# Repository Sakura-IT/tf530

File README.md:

# TF530 Revision 3

WARNING: This board has not been CE tested. It may cause damage to your A500. I take no responsibility for this. 

This repository contains all the files needed to produce a copy of my accelerator board.

The CPLD Required is a XC9572XL-10VQ64.  The CPLD XC9572XL-10VQG64 is the readily available RoHS "Green" lead-free equivalent.

Everything in this repository is released under the GNU GPLv2. You may create or base commercial PCBs from the work in this repository but you must make the sources for all derivative work available. I have noticed some forks have removed copyright notices. This is a breach of the GPL.

## Firmware / Requirements

  * Xilinx ISE, 14.7 (the final version - other versions may work but this is the one I support)
  * JTAG Adaptor

[For more information visit my channel](https://www.youtube.com/c/TerribleFire)

## License

This project and all the files contained are released under the GNU GPLv2. If you build a modified version of the board you must supply the end user with all the sources (this can be a web link).

## The TerribleFire 530 board (Revision 3)

Completely untested board link.... use with caution!!!! Do not come crying to me if it didnt work!!

http://dirtypcbs.com/store/designer/details/12476/2654/tf530-rev3-zip

## The TerribleFire 530 board (Revision 2)

This board is now in Beta. It may not work in all circumstances but it has been verified to boot AmigaOS 1.3, 2.05 and 3.1 and run various games and desktop apps at 25Mhz. Operation is not guarunteed to be crash free but will work in most "happy path" situations.

I have only verified the HD interface with Compact Flash cards.
I have verified this board boots on Amiga 500 Rev 5, 6a, 8.1a

I accept no responsibiltiy for any damage to any equipment that results from the use of this board. IT IS ENTIRELY AT YOUR OWN RISK!

## Installation

As of Revision 3 installation no longer needs the OVR and INT2 signals connected to the Amiga motherboard. The headers remain on the TF530 for testing but do not need to be connected although it should make little difference if they are connected. Well behaved Autoconfig devices will work alongside the TF530. The autoconfig space asserts the internal OVR signal when there are PICs remaining to be configured. After which the autoconfig will probe the standard bus. This revision should work on the A2000 (untested).

IPL0 has not been routed because we only ever need to assert INT2 and/or INT6.

## What does the board look like

The TF530 Rev 3 looks like...

## The Rev 3 BOM (WARNING! This is untested)

| Qty | Value           | Device             | Package              | Parts                                                            | Description                   |
|-----|-----------------|--------------------|----------------------|------------------------------------------------------------------|-------------------------------|
| 1   |                 | MC68030RC          | MPGA128              | IC1                                                              | 68030 PROCESSOR               |
| 1   |                 | MC68882FN          | PLCC68-S             | IC2                                                              | 68882 CO-PROCESSOR (FPU) + PLCC68 Thru Hole Socket |
| 2   | 0.1uF           | 0.1UF-25V(+80/-20%)| 0603-CAP             | C16, C17                                                         | CAP-00810                     |
| 15  | 10uF            | CAP_CERAMIC1206    | 1206                 | C1, C2, C3, C4, C5, C6, C7, C8, C9, C10, C11, C12, C13, C14, C15 | Ceramic Capacitors            |
| 3   | 1K              | RESISTOR1206       | 1206                 | R1, R2, R3                                                                  | Resistors                     |
| 2   | 74LVC1G17DBV    | 74LVC1G17DBV       | SOT23-5              | IC4, IC5                                                         | Single Schmitt-Trigger Buffer |
| 4   | AS7C4096A-12TCN | AS7C4096A-12TCN    | TSOP44-II            | IC6, IC7, IC8, IC9                                               | SRAM 512k x 8, 5V DO NOT USE ISSI Chips!!      |
| 1   | BYPASS          | JUMPER-2PTH        | 1X02                 | BYPASS                                                           | Jumper                        |
| 3   | CAY16-102J4LF   | CAY16-102J4LF      | RESCAXE80P320X160-8N | RN1, RN2, RN3                                                    | Res Thick Film Array 1K Ohm  |
| 1   | CDIS            | JUMPER-2PTH        | 1X02                 | JP5                                                              | Jumper                        |
| 1   | CLOCKSEL        | JUMPER-3PTH        | 1X03                 | JP1                                                              | Jumper                        |
| 1   | EXT5V           | JUMPER-2PTH        | 1X02                 | PWR1                                                             | Jumper                        |
| 1   | IDE CONNECTOR   | PINHD-2X20         | 2X20                 | IDECONNECTOR                                                     | PIN HEADER                    |
| 1   | INF             | 0.05OHM-1/5W-1%    | 0603                 | RCLKLOAD                                                         | Not Required - Experimental   |
| 1   | JTAG            | HEADER-1X6ROUND    | 1X06_ROUND           | JTAG                                                             | PIN HEADER                    |
| 1   | LM1117-3.3      | V_REG_LM1117SOT223 | SOT223               | IC3                                                              | 3.3V Voltage Regulator LM1117 |
| 1   | MC68000         | MC68000P           | DIL64                | X1                                                               | 68xxx CPU Slot Strip Headers  |
| 1   | MMUDIS          | JUMPER-2PTH        | 1X02                 | JP3                                                              | Jumper                        |
| 1   | SPI PORT        | PINHD-2X6          | 2X06                 | SPIPORT                                                          | PIN HEADER                    |
| 1   | TP1             | JUMPER-2PTH        | 1X02                 | TP1                                                              | Jumper                        |
| 1   | X25MHZ          | OSCILLATOR         | OSC_7X5MM            | OSC1                                                             | Oscillator e.g. 25MHz         |
| 2   | XC9572XL-VQ64   | XC9572XL-VQ64      | VQ64                 | XC9572XL(BUS), XC9572XL(RAM)                                     | Xilinx CPLD                   |

### Notes

* _The CPU and (optional) FPU must be 25MHz/33Mhz capable._

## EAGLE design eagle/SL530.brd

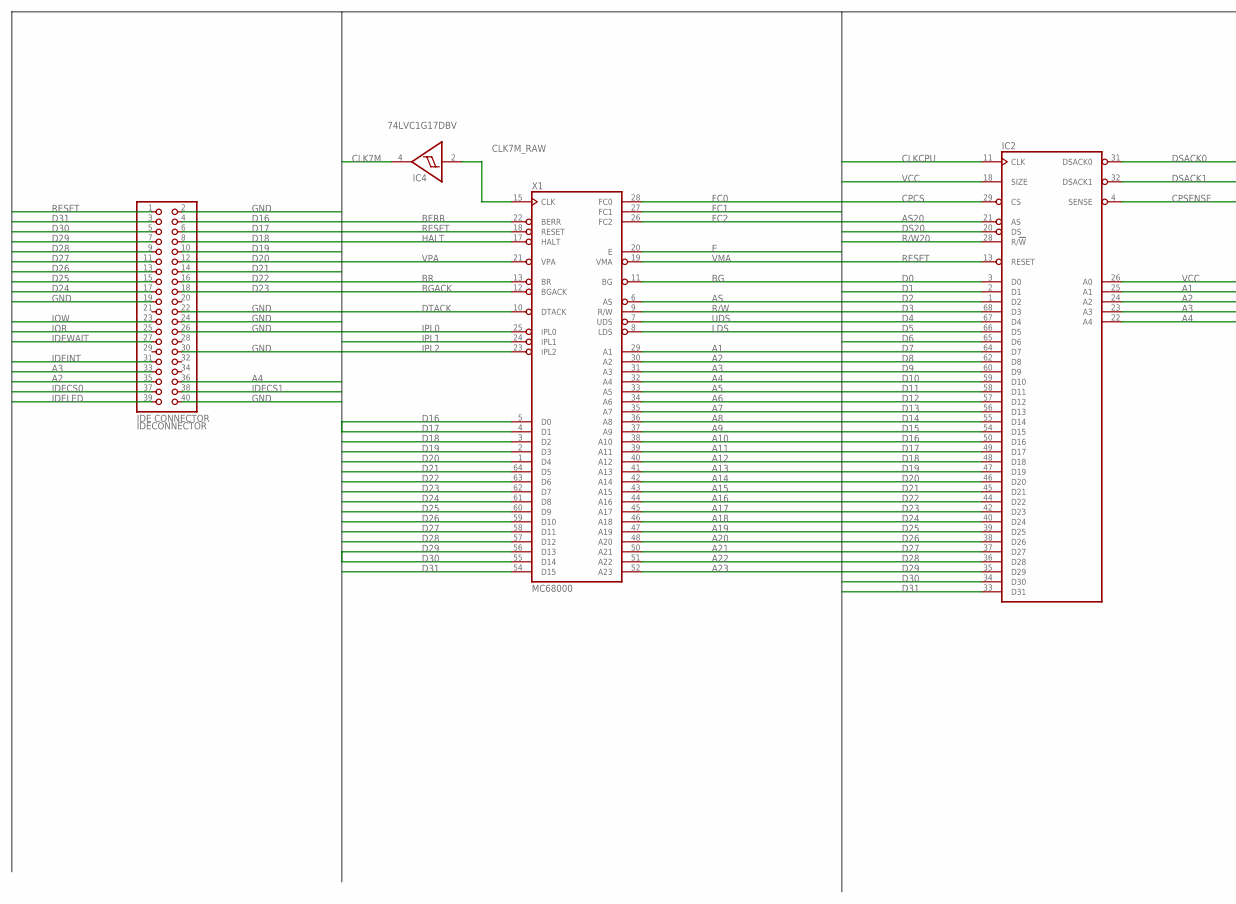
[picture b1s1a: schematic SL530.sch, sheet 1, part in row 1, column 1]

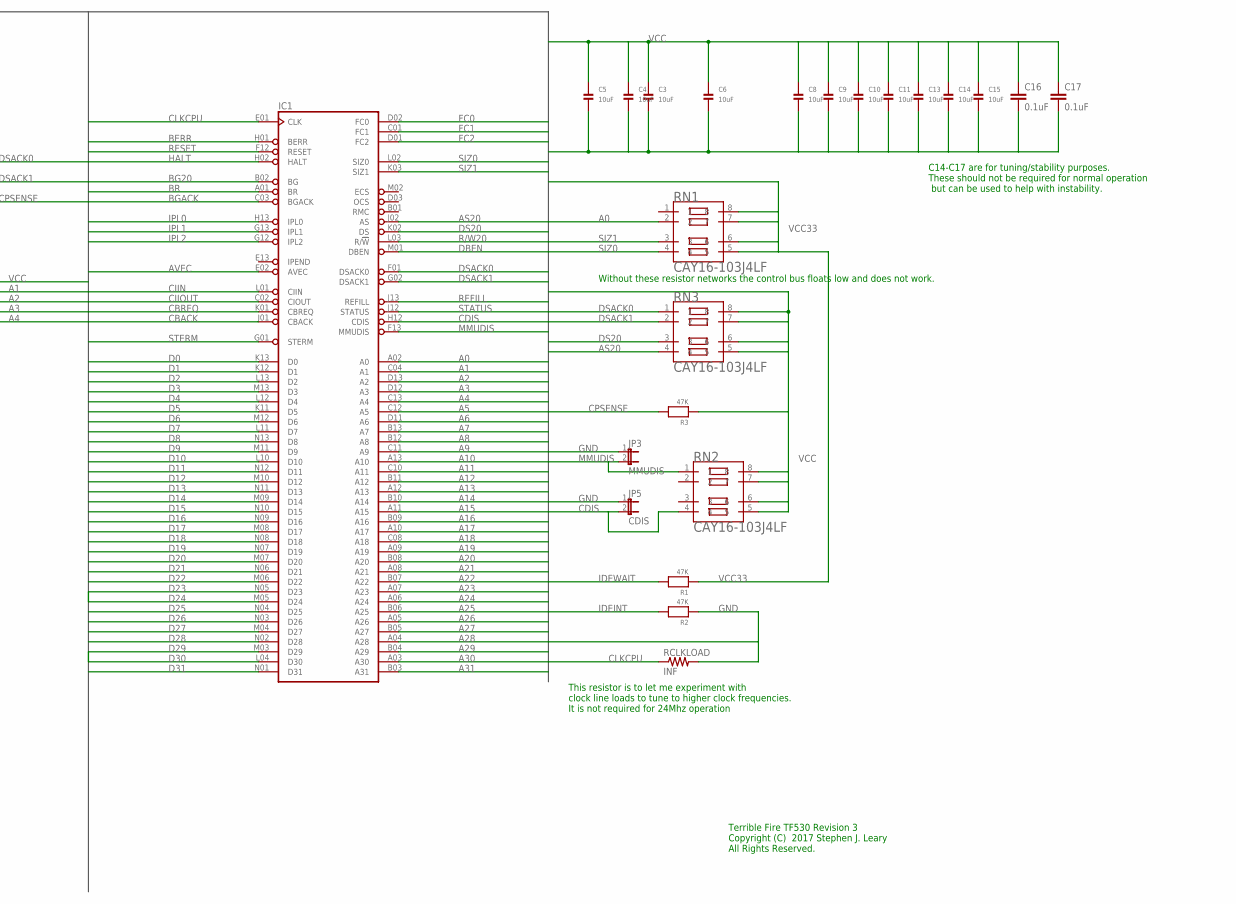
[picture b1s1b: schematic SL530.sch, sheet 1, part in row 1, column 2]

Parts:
C3, C4, C5, C6, C8, C9, C10, C11, C13, C14, C15: 10uF; 1206
C16, C17: 0.1uF; 0603-CAP
IC1: MC68030RC; MPGA128
IC2: MC68881FN-SOC; PLCC68-S
IC4: 74LVC1G17DBV; SOT23-5
IDECONNECTOR: IDE CONNECTOR; 2X20
JP3: MMUDIS; 1X02
JP5: CDIS; 1X02
R1, R2, R3: 47K; 1206
RCLKLOAD: INF; 0603
RN1, RN2, RN3: CAY16-103J4LF; RESCAXE80P320X160-8N
X1: MC68000; DIL64

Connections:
A0: IC1.A02 (A0), RN1.2; also elsewhere on the board
A1: IC1.C04 (A1), IC2.25 (A1), X1.29 (A1); also elsewhere on the board
A2: IC1.D13 (A2), IC2.24 (A2), IDECONNECTOR.35, X1.30 (A2); also elsewhere on the board
A3: IC1.D12 (A3), IC2.23 (A3), IDECONNECTOR.33, X1.31 (A3); also elsewhere on the board
A4: IC1.C13 (A4), IC2.22 (A4), IDECONNECTOR.36, X1.32 (A4); also elsewhere on the board
A5: IC1.C12 (A5), X1.33 (A5); also elsewhere on the board
A6: IC1.D11 (A6), X1.34 (A6); also elsewhere on the board
A7: IC1.B13 (A7), X1.35 (A7); also elsewhere on the board
A8: IC1.B12 (A8), X1.36 (A8); also elsewhere on the board
A9: IC1.C11 (A9), X1.37 (A9); also elsewhere on the board
A10: IC1.A13 (A10), X1.38 (A10); also elsewhere on the board
A11: IC1.C10 (A11), X1.39 (A11); also elsewhere on the board
A12: IC1.B11 (A12), X1.40 (A12); also elsewhere on the board
A13: IC1.A12 (A13), X1.41 (A13); also elsewhere on the board
A14: IC1.B10 (A14), X1.42 (A14); also elsewhere on the board
A15: IC1.A11 (A15), X1.43 (A15); also elsewhere on the board
A16: IC1.B09 (A16), X1.44 (A16); also elsewhere on the board
A17: IC1.A10 (A17), X1.45 (A17); also elsewhere on the board
A18: IC1.C08 (A18), X1.46 (A18); also elsewhere on the board
A19: IC1.A09 (A19), X1.47 (A19); also elsewhere on the board
A20: IC1.B08 (A20), X1.48 (A20); also elsewhere on the board
A21: IC1.A08 (A21), X1.50 (A21); also elsewhere on the board
A22: IC1.B07 (A22), X1.51 (A22); also elsewhere on the board
A23: IC1.A07 (A23), X1.52 (A23); also elsewhere on the board
A24: IC1.A06 (A24)
A25: IC1.B06 (A25)
A26: IC1.A05 (A26)
A27: IC1.B05 (A27)
A28: IC1.A04 (A28)
A29: IC1.B04 (A29)
A30: IC1.A03 (A30)
A31: IC1.B03 (A31)
AS: X1.6 (AS); also elsewhere on the board
AS20: IC1.J02 (AS), IC2.21 (AS), RN3.4; also elsewhere on the board
AVEC: IC1.E02 (AVEC); also elsewhere on the board
BERR: IC1.H01 (BERR), X1.22 (BERR); also elsewhere on the board
BG: X1.11 (BG); also elsewhere on the board
BG20: IC1.B02 (BG); also elsewhere on the board
BGACK: IC1.C03 (BGACK), X1.12 (BGACK); also elsewhere on the board
BR: IC1.A01 (BR), X1.13 (BR)
CBACK: IC1.J01 (CBACK); also elsewhere on the board
CBREQ: IC1.K01 (CBREQ); also elsewhere on the board
CDIS: IC1.H12 (CDIS), JP5.2, RN2.4
CIIN: IC1.L01 (CIIN); also elsewhere on the board
CIIOUT: IC1.C02 (CIOUT)
CLK7M: IC4.4 (O); also elsewhere on the board
CLK7M_RAW: IC4.2 (I), X1.15 (CLK)
CLKCPU: IC1.E01 (CLK), IC2.11 (CLK), RCLKLOAD.1; also elsewhere on the board
CPCS: IC2.29 (CS); also elsewhere on the board
CPSENSE: IC2.4 (SENSE), R3.2; also elsewhere on the board
D0: IC1.K13 (D0), IC2.3 (D0); also elsewhere on the board
D1: IC1.K12 (D1), IC2.2 (D1); also elsewhere on the board
D2: IC1.L13 (D2), IC2.1 (D2); also elsewhere on the board
D3: IC1.M13 (D3), IC2.68 (D3); also elsewhere on the board
D4: IC1.L12 (D4), IC2.67 (D4); also elsewhere on the board
D5: IC1.K11 (D5), IC2.66 (D5); also elsewhere on the board
D6: IC1.M12 (D6), IC2.65 (D6); also elsewhere on the board
D7: IC1.L11 (D7), IC2.64 (D7); also elsewhere on the board
D8: IC1.N13 (D8), IC2.62 (D8); also elsewhere on the board
D9: IC1.M11 (D9), IC2.60 (D9); also elsewhere on the board
D10: IC1.L10 (D10), IC2.59 (D10); also elsewhere on the board
D11: IC1.N12 (D11), IC2.58 (D11); also elsewhere on the board
D12: IC1.M10 (D12), IC2.57 (D12); also elsewhere on the board
D13: IC1.N11 (D13), IC2.56 (D13); also elsewhere on the board
D14: IC1.M09 (D14), IC2.55 (D14); also elsewhere on the board
D15: IC1.N10 (D15), IC2.54 (D15); also elsewhere on the board
D16: IC1.N09 (D16), IC2.50 (D16), IDECONNECTOR.4, X1.5 (D0); also elsewhere on the board
D17: IC1.M08 (D17), IC2.49 (D17), IDECONNECTOR.6, X1.4 (D1); also elsewhere on the board
D18: IC1.N08 (D18), IC2.48 (D18), IDECONNECTOR.8, X1.3 (D2); also elsewhere on the board
D19: IC1.N07 (D19), IC2.47 (D19), IDECONNECTOR.10, X1.2 (D3); also elsewhere on the board
D20: IC1.M07 (D20), IC2.46 (D20), IDECONNECTOR.12, X1.1 (D4); also elsewhere on the board
D21: IC1.N06 (D21), IC2.45 (D21), IDECONNECTOR.14, X1.64 (D5); also elsewhere on the board
D22: IC1.M06 (D22), IC2.44 (D22), IDECONNECTOR.16, X1.63 (D6); also elsewhere on the board
D23: IC1.N05 (D23), IC2.42 (D23), IDECONNECTOR.18, X1.62 (D7); also elsewhere on the board
D24: IC1.M05 (D24), IC2.40 (D24), IDECONNECTOR.17, X1.61 (D8); also elsewhere on the board
D25: IC1.N04 (D25), IC2.39 (D25), IDECONNECTOR.15, X1.60 (D9); also elsewhere on the board
D26: IC1.N03 (D26), IC2.38 (D26), IDECONNECTOR.13, X1.59 (D10); also elsewhere on the board
D27: IC1.M04 (D27), IC2.37 (D27), IDECONNECTOR.11, X1.58 (D11); also elsewhere on the board
D28: IC1.N02 (D28), IC2.36 (D28), IDECONNECTOR.9, X1.57 (D12); also elsewhere on the board
D29: IC1.M03 (D29), IC2.35 (D29), IDECONNECTOR.7, X1.56 (D13); also elsewhere on the board
D30: IC1.L04 (D30), IC2.34 (D30), IDECONNECTOR.5, X1.55 (D14); also elsewhere on the board
D31: IC1.N01 (D31), IC2.33 (D31), IDECONNECTOR.3, X1.54 (D15); also elsewhere on the board
DBEN: IC1.M01 (DBEN)
DS20: IC1.K02 (DS), IC2.20 (DS), RN3.3; also elsewhere on the board
DSACK0: IC1.F01 (DSACK0), IC2.31 (DSACK0), RN3.1
DSACK1: IC1.G02 (DSACK1), IC2.32 (DSACK1), RN3.2; also elsewhere on the board
DTACK: X1.10 (DTACK); also elsewhere on the board
E: X1.20 (E); also elsewhere on the board
FC0: IC1.D02 (FC0), X1.28 (FC0); also elsewhere on the board
FC1: IC1.C01 (FC1), X1.27 (FC1); also elsewhere on the board
FC2: IC1.D01 (FC2), X1.26 (FC2); also elsewhere on the board
GND: C3.2, C4.2, C5.2, C6.2, C8.2, C9.2, C10.2, C11.2, C13.2, C14.2, C15.2, C16.2, C17.2, IC1.C05 (GND), IC1.C07 (GND), IC1.C09 (GND), IC1.E03 (GND), IC1.E11 (GND), IC1.F03 (GND), IC1.G03 (GND), IC1.G11 (GND), IC1.J03 (GND), IC1.J11 (GND), IC1.L05 (GND), IC1.L07 (GND), IC1.L08 (GND), IC1.L09 (GND), IC2.5 (GND), IC2.6 (GND), IC2.7 (GND), IC2.8 (GND), IC2.9 (GND), IC2.12 (GND), IC2.14 (GND), IC2.19 (GND), IC2.30 (GND), IC2.41 (GND), IC2.51 (GND), IC2.63 (GND), IC4.3 (GND), IDECONNECTOR.2, IDECONNECTOR.19, IDECONNECTOR.22, IDECONNECTOR.24, IDECONNECTOR.26, IDECONNECTOR.30, IDECONNECTOR.40, JP3.1, JP5.1, R2.1, RCLKLOAD.2, X1.16 (GND), X1.53 (GND); also elsewhere on the board
HALT: IC1.H02 (HALT), X1.17 (HALT); also elsewhere on the board
IDECS0: IDECONNECTOR.37; also elsewhere on the board
IDECS1: IDECONNECTOR.38; also elsewhere on the board
IDEINT: IDECONNECTOR.31, R2.2; also elsewhere on the board
IDELED: IDECONNECTOR.39
IDEWAIT: IDECONNECTOR.27, R1.2; also elsewhere on the board
IOR: IDECONNECTOR.25; also elsewhere on the board
IOW: IDECONNECTOR.23; also elsewhere on the board
IPL0: IC1.H13 (IPL0), X1.25 (IPL0)
IPL1: IC1.G13 (IPL1), X1.24 (IPL1); also elsewhere on the board
IPL2: IC1.G12 (IPL2), X1.23 (IPL2); also elsewhere on the board
LDS: X1.8 (LDS); also elsewhere on the board
MMUDIS: IC1.F13 (MMUDIS), JP3.2, RN2.1
R/W: X1.9 (R/W); also elsewhere on the board
R/W20: IC1.L03 (R/!W), IC2.28 (R/!W); also elsewhere on the board
REFILL: IC1.J13 (REFILL)
RESET: IC1.F12 (RESET), IC2.13 (RESET), IDECONNECTOR.1, X1.18 (RESET); also elsewhere on the board
SIZ0: IC1.L02 (SIZ0), RN1.4; also elsewhere on the board
SIZ1: IC1.K03 (SIZ1), RN1.3; also elsewhere on the board
STATUS: IC1.J12 (STATUS)
STERM: IC1.G01 (STERM); also elsewhere on the board
UDS: X1.7 (UDS); also elsewhere on the board
VCC: C3.1, C4.1, C5.1, C6.1, C8.1, C9.1, C10.1, C11.1, C13.1, C14.1, C15.1, C16.1, C17.1, IC1.C06 (VCC), IC1.D04 (VCC), IC1.D10 (VCC), IC1.F02 (VCC), IC1.F11 (VCC), IC1.H03 (VCC), IC1.H11 (VCC), IC1.K04 (VCC), IC1.K10 (VCC), IC1.L06 (VCC), IC2.10 (VCC), IC2.16 (VCC), IC2.17 (VCC), IC2.18 (SIZE), IC2.26 (A0), IC2.27 (VCC), IC2.43 (VCC), IC2.52 (VCC), IC2.53 (VCC), IC2.61 (VCC), IC4.5 (VCC), R3.1, RN2.5, RN2.6, RN2.7, RN2.8, RN3.5, RN3.6, RN3.7, RN3.8, X1.14 (VCC), X1.49 (VCC); also elsewhere on the board
VCC33: R1.1, RN1.5, RN1.6, RN1.7, RN1.8; also elsewhere on the board
VMA: X1.19 (VMA); also elsewhere on the board
VPA: X1.21 (VPA); also elsewhere on the board

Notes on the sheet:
This resistor is to let me experiment with clock line loads to tune to higher clock frequencies. It is not required for 24Mhz operation
C14-C17 are for tuning/stability purposes. These should not be required for normal operation but can be used to help with instability.
Without these resistor networks the control bus floats low and does not work.
Terrible Fire TF530 Revision 3 Copyright (C) 2017 Stephen J. Leary All Rights Reserved.

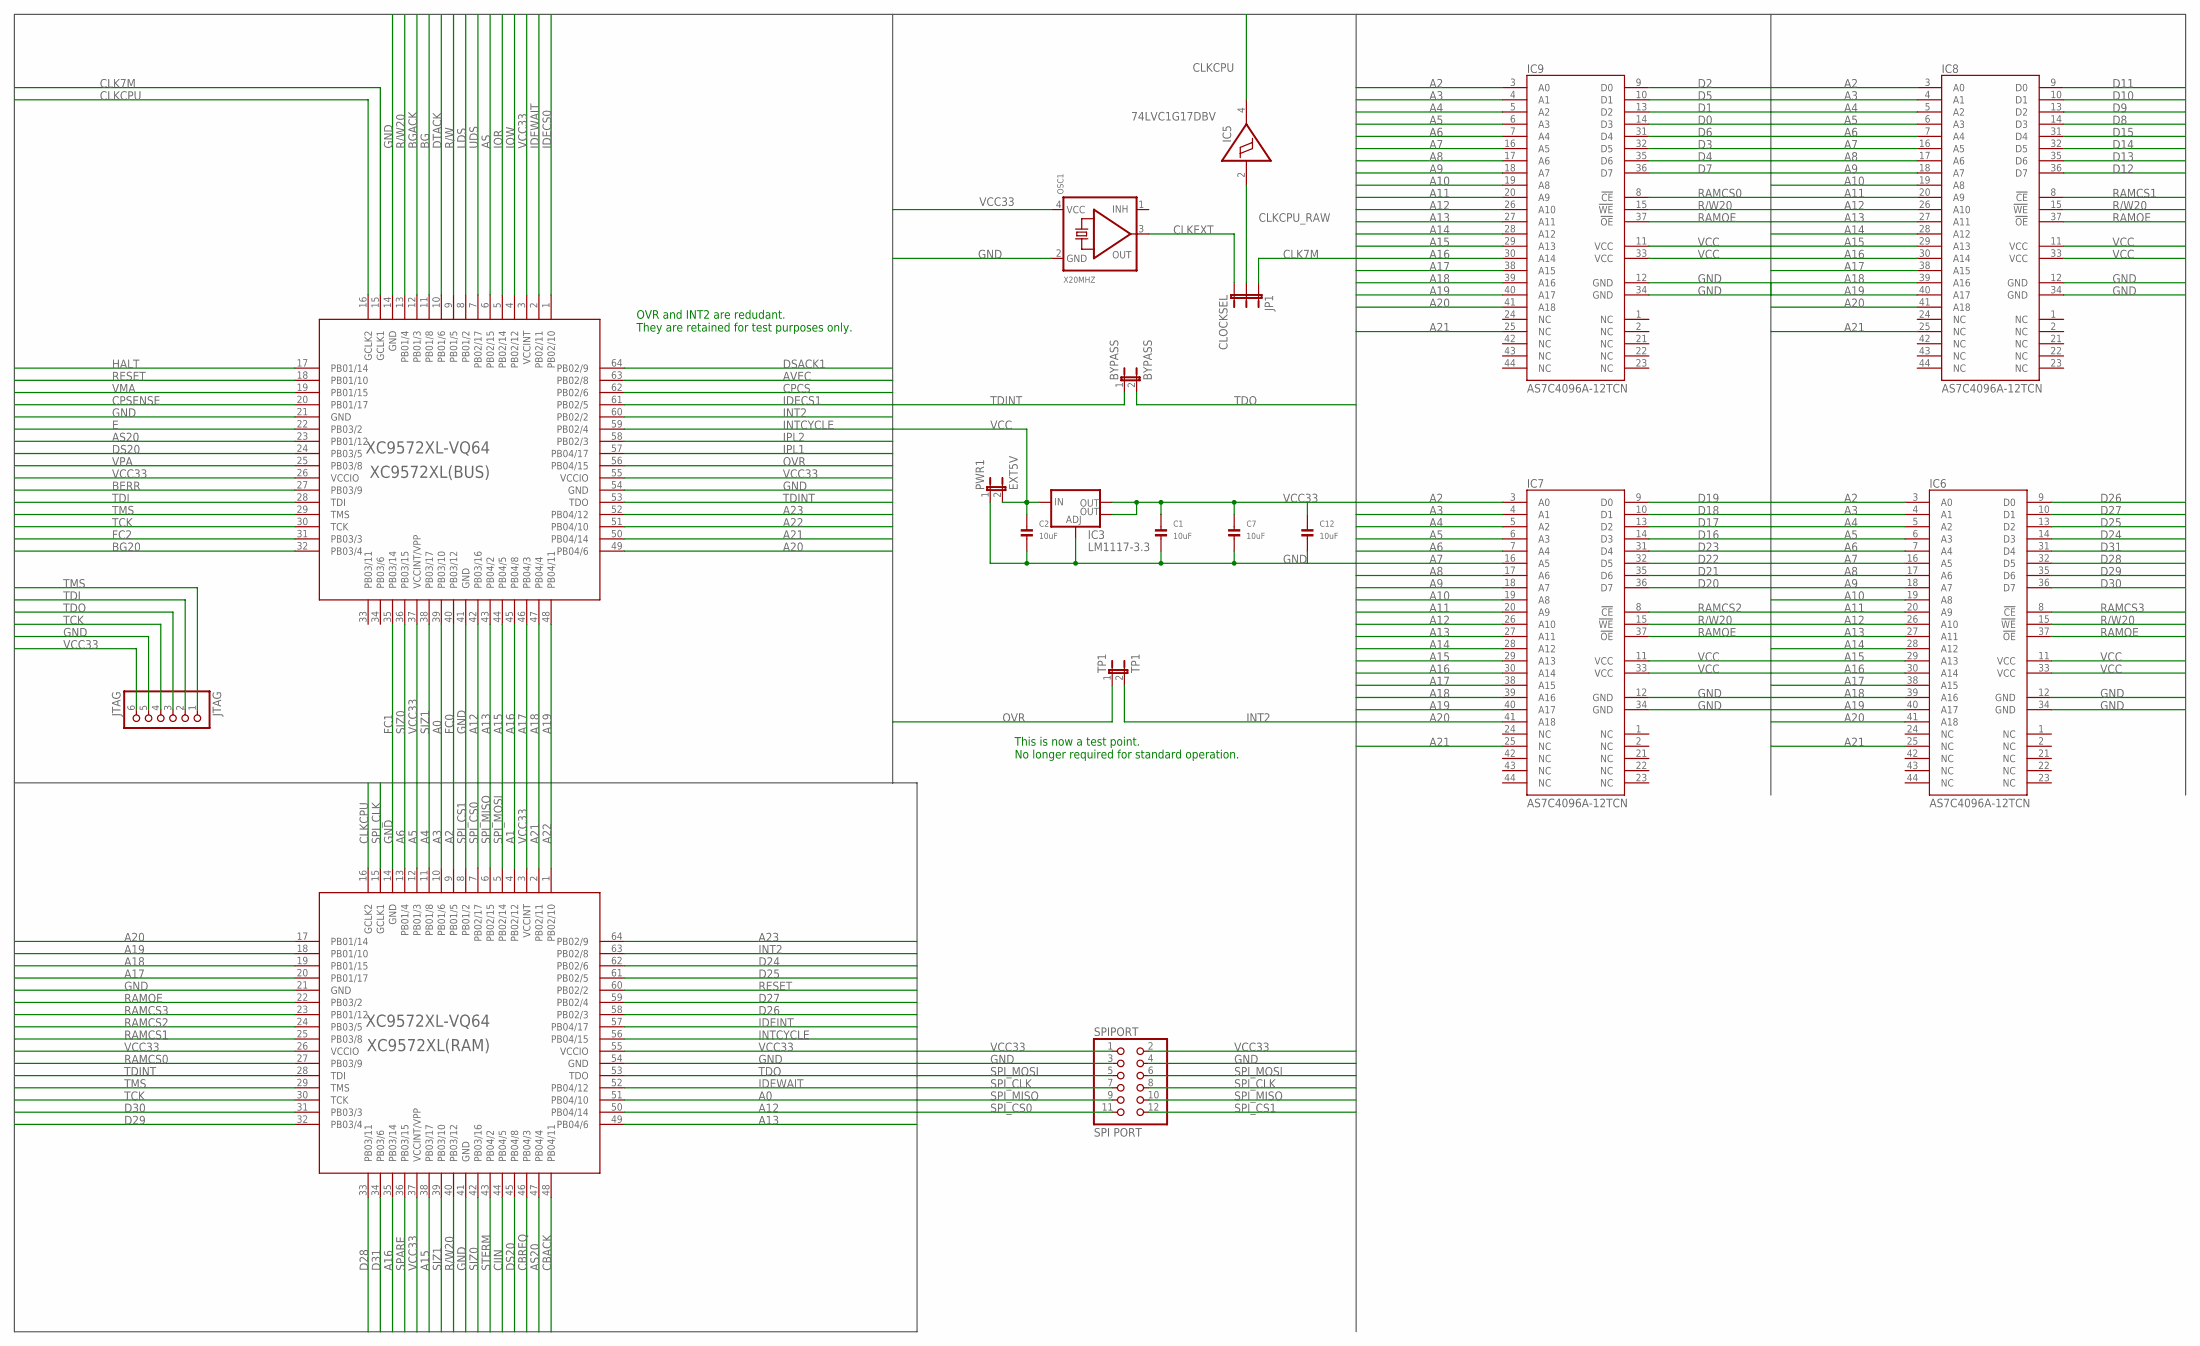
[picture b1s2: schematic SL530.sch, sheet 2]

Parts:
BYPASS: BYPASS; 1X02
C1, C2, C7, C12: 10uF; 1206
IC3: LM1117-3.3; SOT223
IC5: 74LVC1G17DBV; SOT23-5
IC6, IC7, IC8, IC9: AS7C4096A-12TCN; TSOP44-II
JP1: CLOCKSEL; 1X03
JTAG: JTAG; 1X06_ROUND
OSC1: X20MHZ; OSC_7X5MM
PWR1: EXT5V; 1X02
SPIPORT: SPI PORT; 2X06
TP1: TP1; 1X02
XC9572XL(BUS), XC9572XL(RAM): XC9572XL-VQ64; VQ64

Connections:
A0: XC9572XL(BUS).39 (PB03/10), XC9572XL(RAM).51 (PB04/10); also elsewhere on the board
A1: XC9572XL(RAM).4 (PB02/12); also elsewhere on the board
A2: IC6.3 (A0), IC7.3 (A0), IC8.3 (A0), IC9.3 (A0), XC9572XL(RAM).9 (PB01/5); also elsewhere on the board
A3: IC6.4 (A1), IC7.4 (A1), IC8.4 (A1), IC9.4 (A1), XC9572XL(RAM).10 (PB01/6); also elsewhere on the board
A4: IC6.5 (A2), IC7.5 (A2), IC8.5 (A2), IC9.5 (A2), XC9572XL(RAM).11 (PB01/8); also elsewhere on the board
A5: IC6.6 (A3), IC7.6 (A3), IC8.6 (A3), IC9.6 (A3), XC9572XL(RAM).12 (PB01/3); also elsewhere on the board
A6: IC6.7 (A4), IC7.7 (A4), IC8.7 (A4), IC9.7 (A4), XC9572XL(RAM).13 (PB01/4); also elsewhere on the board
A7: IC6.16 (A5), IC7.16 (A5), IC8.16 (A5), IC9.16 (A5); also elsewhere on the board
A8: IC6.17 (A6), IC7.17 (A6), IC8.17 (A6), IC9.17 (A6); also elsewhere on the board
A9: IC6.18 (A7), IC7.18 (A7), IC8.18 (A7), IC9.18 (A7); also elsewhere on the board
A10: IC6.19 (A8), IC7.19 (A8), IC8.19 (A8), IC9.19 (A8); also elsewhere on the board
A11: IC6.20 (A9), IC7.20 (A9), IC8.20 (A9), IC9.20 (A9); also elsewhere on the board
A12: IC6.26 (A10), IC7.26 (A10), IC8.26 (A10), IC9.26 (A10), XC9572XL(BUS).42 (PB03/16), XC9572XL(RAM).50 (PB04/14); also elsewhere on the board
A13: IC6.27 (A11), IC7.27 (A11), IC8.27 (A11), IC9.27 (A11), XC9572XL(BUS).43 (PB04/2), XC9572XL(RAM).49 (PB04/6); also elsewhere on the board
A14: IC6.28 (A12), IC7.28 (A12), IC8.28 (A12), IC9.28 (A12); also elsewhere on the board
A15: IC6.29 (A13), IC7.29 (A13), IC8.29 (A13), IC9.29 (A13), XC9572XL(BUS).44 (PB04/5), XC9572XL(RAM).38 (PB03/17); also elsewhere on the board
A16: IC6.30 (A14), IC7.30 (A14), IC8.30 (A14), IC9.30 (A14), XC9572XL(BUS).45 (PB04/8), XC9572XL(RAM).35 (PB03/14); also elsewhere on the board
A17: IC6.38 (A15), IC7.38 (A15), IC8.38 (A15), IC9.38 (A15), XC9572XL(BUS).46 (PB04/3), XC9572XL(RAM).20 (PB01/17); also elsewhere on the board
A18: IC6.39 (A16), IC7.39 (A16), IC8.39 (A16), IC9.39 (A16), XC9572XL(BUS).47 (PB04/4), XC9572XL(RAM).19 (PB01/15); also elsewhere on the board
A19: IC6.40 (A17), IC7.40 (A17), IC8.40 (A17), IC9.40 (A17), XC9572XL(BUS).48 (PB04/11), XC9572XL(RAM).18 (PB01/10); also elsewhere on the board
A20: IC6.41 (A18), IC7.41 (A18), IC8.41 (A18), IC9.41 (A18), XC9572XL(BUS).49 (PB04/6), XC9572XL(RAM).17 (PB01/14); also elsewhere on the board
A21: IC6.25 (NC), IC7.25 (NC), IC8.25 (NC), IC9.25 (NC), XC9572XL(BUS).50 (PB04/14), XC9572XL(RAM).2 (PB02/11); also elsewhere on the board
A22: XC9572XL(BUS).51 (PB04/10), XC9572XL(RAM).1 (PB02/10); also elsewhere on the board
A23: XC9572XL(BUS).52 (PB04/12), XC9572XL(RAM).64 (PB02/9); also elsewhere on the board
AS: XC9572XL(BUS).6 (PB02/15); also elsewhere on the board
AS20: XC9572XL(BUS).23 (PB01/12), XC9572XL(RAM).47 (PB04/4); also elsewhere on the board
AVEC: XC9572XL(BUS).63 (PB02/8); also elsewhere on the board
BERR: XC9572XL(BUS).27 (PB03/9); also elsewhere on the board
BG: XC9572XL(BUS).11 (PB01/8); also elsewhere on the board
BG20: XC9572XL(BUS).32 (PB03/4); also elsewhere on the board
BGACK: XC9572XL(BUS).12 (PB01/3); also elsewhere on the board
CBACK: XC9572XL(RAM).48 (PB04/11); also elsewhere on the board
CBREQ: XC9572XL(RAM).46 (PB04/3); also elsewhere on the board
CIIN: XC9572XL(RAM).44 (PB04/5); also elsewhere on the board
CLK7M: JP1.1, XC9572XL(BUS).15 (GCLK1); also elsewhere on the board
CLKCPU: IC5.4 (O), XC9572XL(BUS).16 (GCLK2), XC9572XL(RAM).16 (GCLK2); also elsewhere on the board
CLKCPU_RAW: IC5.2 (I), JP1.2
CLKEXT: JP1.3, OSC1.3 (OUT)
CPCS: XC9572XL(BUS).62 (PB02/6); also elsewhere on the board
CPSENSE: XC9572XL(BUS).20 (PB01/17); also elsewhere on the board
D0: IC9.14 (D3); also elsewhere on the board
D1: IC9.13 (D2); also elsewhere on the board
D2: IC9.9 (D0); also elsewhere on the board
D3: IC9.32 (D5); also elsewhere on the board
D4: IC9.35 (D6); also elsewhere on the board
D5: IC9.10 (D1); also elsewhere on the board
D6: IC9.31 (D4); also elsewhere on the board
D7: IC9.36 (D7); also elsewhere on the board
D8: IC8.14 (D3); also elsewhere on the board
D9: IC8.13 (D2); also elsewhere on the board
D10: IC8.10 (D1); also elsewhere on the board
D11: IC8.9 (D0); also elsewhere on the board
D12: IC8.36 (D7); also elsewhere on the board
D13: IC8.35 (D6); also elsewhere on the board
D14: IC8.32 (D5); also elsewhere on the board
D15: IC8.31 (D4); also elsewhere on the board
D16: IC7.14 (D3); also elsewhere on the board
D17: IC7.13 (D2); also elsewhere on the board
D18: IC7.10 (D1); also elsewhere on the board
D19: IC7.9 (D0); also elsewhere on the board
D20: IC7.36 (D7); also elsewhere on the board
D21: IC7.35 (D6); also elsewhere on the board
D22: IC7.32 (D5); also elsewhere on the board
D23: IC7.31 (D4); also elsewhere on the board
D24: IC6.14 (D3), XC9572XL(RAM).62 (PB02/6); also elsewhere on the board
D25: IC6.13 (D2), XC9572XL(RAM).61 (PB02/5); also elsewhere on the board
D26: IC6.9 (D0), XC9572XL(RAM).58 (PB02/3); also elsewhere on the board
D27: IC6.10 (D1), XC9572XL(RAM).59 (PB02/4); also elsewhere on the board
D28: IC6.32 (D5), XC9572XL(RAM).33 (PB03/11); also elsewhere on the board
D29: IC6.35 (D6), XC9572XL(RAM).32 (PB03/4); also elsewhere on the board
D30: IC6.36 (D7), XC9572XL(RAM).31 (PB03/3); also elsewhere on the board
D31: IC6.31 (D4), XC9572XL(RAM).34 (PB03/6); also elsewhere on the board
DS20: XC9572XL(BUS).24 (PB03/5), XC9572XL(RAM).45 (PB04/8); also elsewhere on the board
DSACK1: XC9572XL(BUS).64 (PB02/9); also elsewhere on the board
DTACK: XC9572XL(BUS).10 (PB01/6); also elsewhere on the board
E: XC9572XL(BUS).22 (PB03/2); also elsewhere on the board
FC0: XC9572XL(BUS).40 (PB03/12); also elsewhere on the board
FC1: XC9572XL(BUS).35 (PB03/14); also elsewhere on the board
FC2: XC9572XL(BUS).31 (PB03/3); also elsewhere on the board
GND: C1.2, C2.2, C7.2, C12.2, IC3.1 (ADJ), IC5.3 (GND), IC6.12 (GND), IC6.34 (GND), IC7.12 (GND), IC7.34 (GND), IC8.12 (GND), IC8.34 (GND), IC9.12 (GND), IC9.34 (GND), JTAG.5, OSC1.2 (GND), PWR1.1, SPIPORT.3, SPIPORT.4, XC9572XL(BUS).14 (GND), XC9572XL(BUS).21 (GND), XC9572XL(BUS).41 (GND), XC9572XL(BUS).54 (GND), XC9572XL(RAM).14 (GND), XC9572XL(RAM).21 (GND), XC9572XL(RAM).41 (GND), XC9572XL(RAM).54 (GND); also elsewhere on the board
HALT: XC9572XL(BUS).17 (PB01/14); also elsewhere on the board
IDECS0: XC9572XL(BUS).1 (PB02/10); also elsewhere on the board
IDECS1: XC9572XL(BUS).61 (PB02/5); also elsewhere on the board
IDEINT: XC9572XL(RAM).57 (PB04/17); also elsewhere on the board
IDEWAIT: XC9572XL(BUS).2 (PB02/11), XC9572XL(RAM).52 (PB04/12); also elsewhere on the board
INT2: TP1.2, XC9572XL(BUS).60 (PB02/2), XC9572XL(RAM).63 (PB02/8)
INTCYCLE: XC9572XL(BUS).59 (PB02/4), XC9572XL(RAM).56 (PB04/15)
IOR: XC9572XL(BUS).5 (PB02/14); also elsewhere on the board
IOW: XC9572XL(BUS).4 (PB02/12); also elsewhere on the board
IPL1: XC9572XL(BUS).57 (PB04/17); also elsewhere on the board
IPL2: XC9572XL(BUS).58 (PB02/3); also elsewhere on the board
LDS: XC9572XL(BUS).8 (PB01/2); also elsewhere on the board
OVR: TP1.1, XC9572XL(BUS).56 (PB04/15)
R/W: XC9572XL(BUS).9 (PB01/5); also elsewhere on the board
R/W20: IC6.15 (!WE), IC7.15 (!WE), IC8.15 (!WE), IC9.15 (!WE), XC9572XL(BUS).13 (PB01/4), XC9572XL(RAM).40 (PB03/12); also elsewhere on the board
RAMCS0: IC9.8 (!CE), XC9572XL(RAM).27 (PB03/9)
RAMCS1: IC8.8 (!CE), XC9572XL(RAM).25 (PB03/8)
RAMCS2: IC7.8 (!CE), XC9572XL(RAM).24 (PB03/5)
RAMCS3: IC6.8 (!CE), XC9572XL(RAM).23 (PB01/12)
RAMOE: IC6.37 (!OE), IC7.37 (!OE), IC8.37 (!OE), IC9.37 (!OE), XC9572XL(RAM).22 (PB03/2)
RESET: XC9572XL(BUS).18 (PB01/10), XC9572XL(RAM).60 (PB02/2); also elsewhere on the board
SIZ0: XC9572XL(BUS).36 (PB03/15), XC9572XL(RAM).42 (PB03/16); also elsewhere on the board
SIZ1: XC9572XL(BUS).38 (PB03/17), XC9572XL(RAM).39 (PB03/10); also elsewhere on the board
SPARE: XC9572XL(RAM).36 (PB03/15)
SPI_CLK: SPIPORT.7, SPIPORT.8, XC9572XL(RAM).15 (GCLK1)
SPI_CS0: SPIPORT.11, XC9572XL(RAM).7 (PB02/17)
SPI_CS1: SPIPORT.12, XC9572XL(RAM).8 (PB01/2)
SPI_MISO: SPIPORT.9, SPIPORT.10, XC9572XL(RAM).6 (PB02/15)
SPI_MOSI: SPIPORT.5, SPIPORT.6, XC9572XL(RAM).5 (PB02/14)
STERM: XC9572XL(RAM).43 (PB04/2); also elsewhere on the board
TCK: JTAG.4, XC9572XL(BUS).30 (TCK), XC9572XL(RAM).30 (TCK)
TDI: JTAG.2, XC9572XL(BUS).28 (TDI)
TDINT: BYPASS.1, XC9572XL(BUS).53 (TDO), XC9572XL(RAM).28 (TDI)
TDO: BYPASS.2, JTAG.3, XC9572XL(RAM).53 (TDO)
TMS: JTAG.1, XC9572XL(BUS).29 (TMS), XC9572XL(RAM).29 (TMS)
UDS: XC9572XL(BUS).7 (PB02/17); also elsewhere on the board
VCC: C2.1, IC3.3 (IN), IC5.5 (VCC), IC6.11 (VCC), IC6.33 (VCC), IC7.11 (VCC), IC7.33 (VCC), IC8.11 (VCC), IC8.33 (VCC), IC9.11 (VCC), IC9.33 (VCC), PWR1.2; also elsewhere on the board
VCC33: C1.1, C7.1, C12.1, IC3.2 (OUT), IC3.4 (OUT), JTAG.6, OSC1.4 (VCC), SPIPORT.1, SPIPORT.2, XC9572XL(BUS).3 (VCCINT), XC9572XL(BUS).26 (VCCIO), XC9572XL(BUS).37 (VCCINT/VPP), XC9572XL(BUS).55 (VCCIO), XC9572XL(RAM).3 (VCCINT), XC9572XL(RAM).26 (VCCIO), XC9572XL(RAM).37 (VCCINT/VPP), XC9572XL(RAM).55 (VCCIO); also elsewhere on the board
VMA: XC9572XL(BUS).19 (PB01/15); also elsewhere on the board
VPA: XC9572XL(BUS).25 (PB03/8); also elsewhere on the board

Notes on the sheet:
OVR and INT2 are redudant. They are retained for test purposes only.
This is now a test point. No longer required for standard operation.

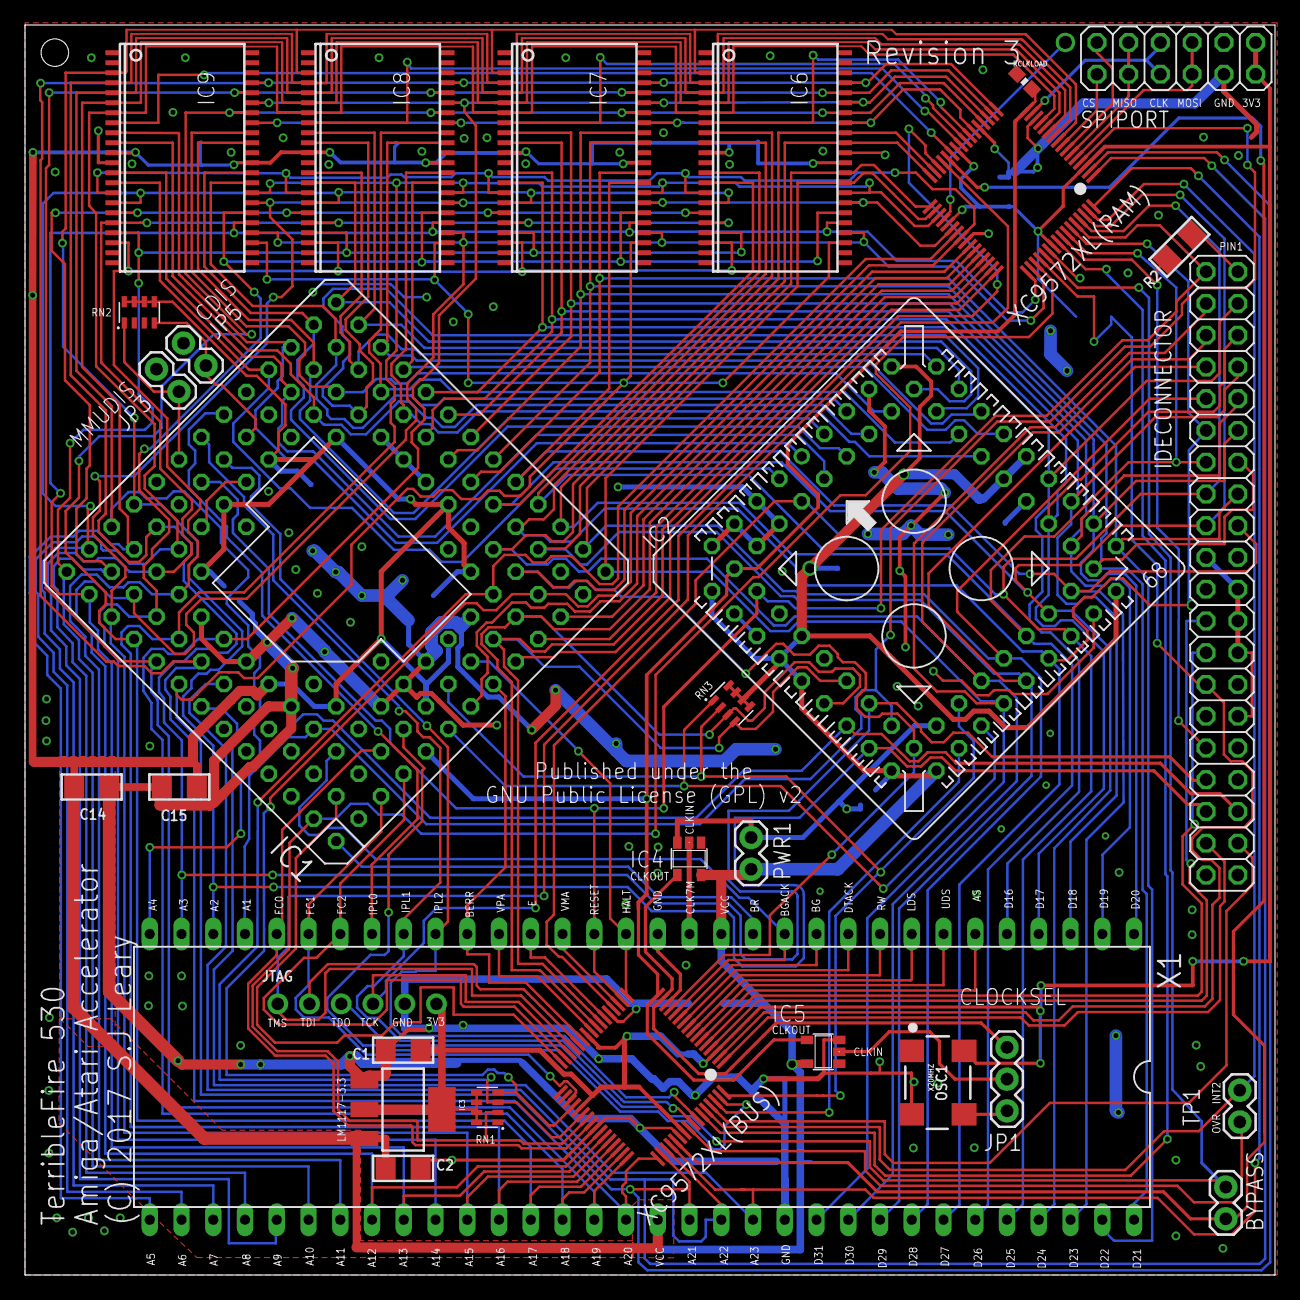
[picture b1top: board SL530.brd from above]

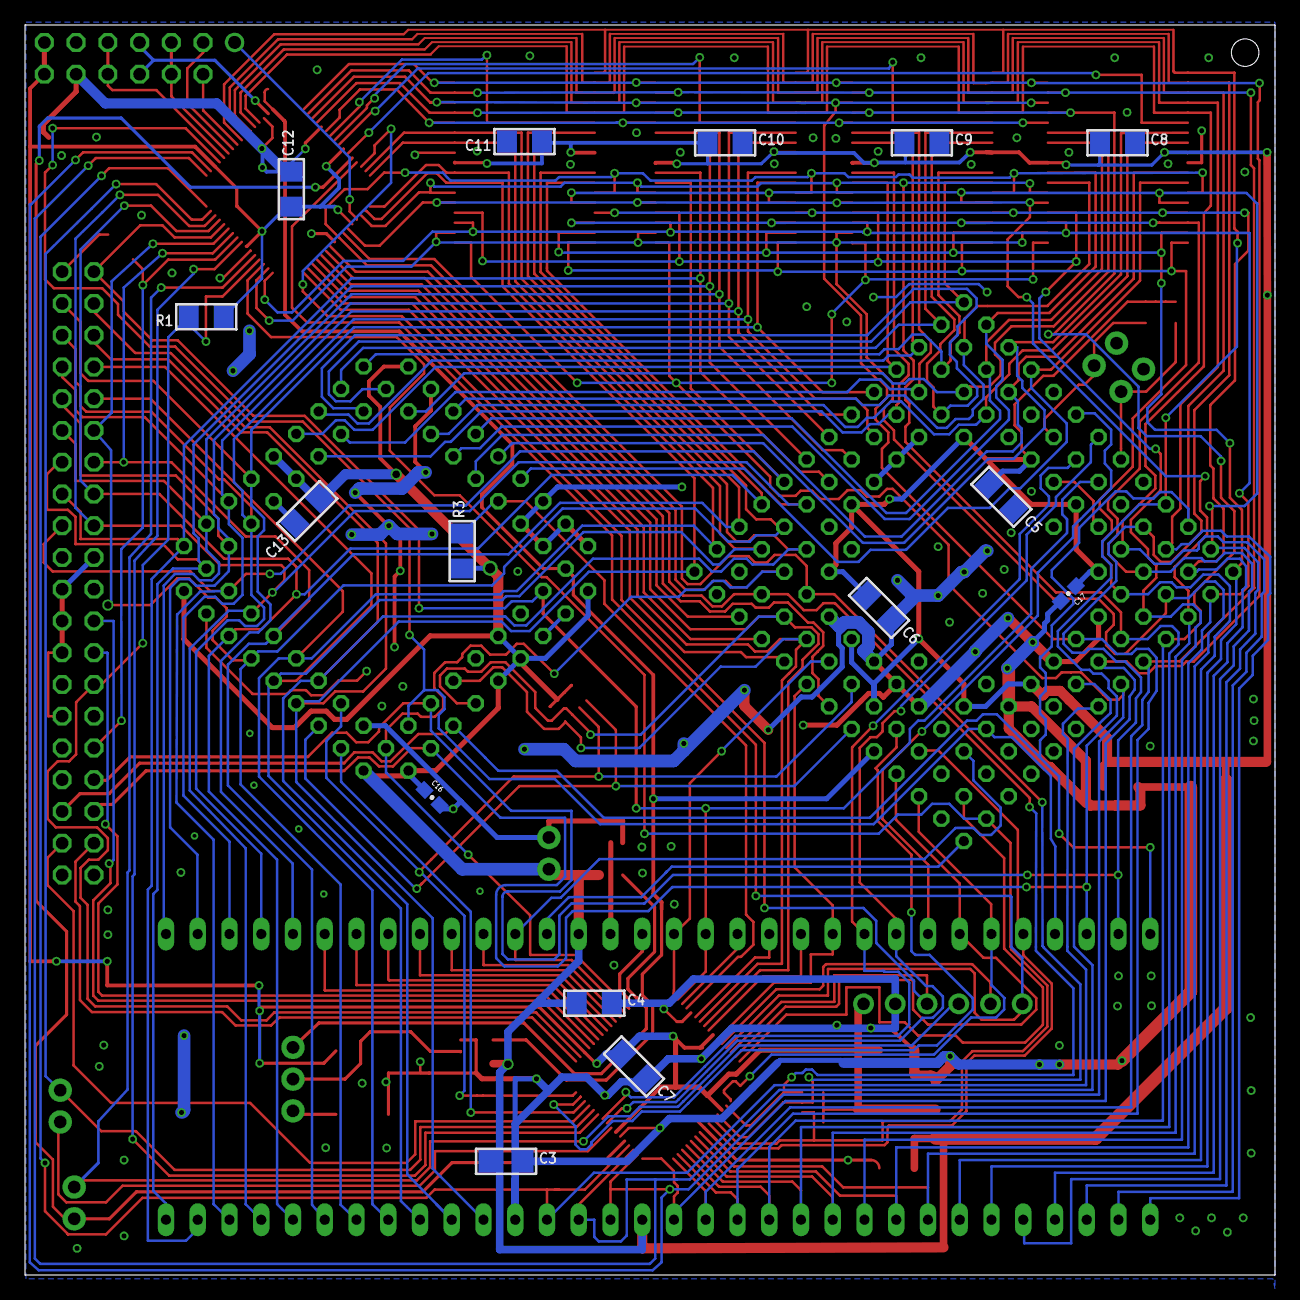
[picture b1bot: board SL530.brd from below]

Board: 2 copper layers, 100.0 x 100.0 mm, 46 parts (15 on the bottom side), 125 nets.

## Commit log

2017-03-26 Create LICENSE
2017-04-13 updated the dot on the silkscreen
2017-04-13 updated the silkscreen
2017-04-13 fixed the silkscreen
2017-04-22 Modifications to the TF530. upgrade to eagle 8. Added IPL lines to the bus CPLD. Significant re-routing of the Bus CPLD traces. Incremented version to revision 3 Beefed up power rails. improved routi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
    No CPLD updates yet.. to follow.
    Added 2 more decoupling caps for the 030
    Removed unused DSACK1/A14/AUX0/AUX1
    I have left in OVR and INT2 for test purposes.
    These shouldn't need connected.
    removed the test traces for A14
2017-04-22 Updating the ucf files for the rev 3.
2017-04-22 Bit of a clean up of the silkscreen Really beefed up VCC to the CPU more ground beefing added an experimental (optional) resistor to load the CPU clock line. added 2 more 0603 caps. One for the CPU a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
    Bit more tidy up on the routing around the bus cpld.
2017-04-22 Dirty PCB images of TF530 Rev 3
2017-06-19 update rev3 bom (untested) (#3)
    * update rev3 bom (untested)
    * Change R1->1K to fix IDEWAIT pullup
2017-12-02 Update Untested BOM (#5)
    One less thing for people to complain about.
2018-01-01 Update README.md
    Correcting error in BOM.
2018-01-09 Pushing the RC1 code
2018-01-09 updating the RC1 firmware
2018-01-10 fixing the bus error signal
2018-01-10 Broken makefile
2018-01-12 Adding zorro console test
2018-01-15 Fixing the ROM cache code
2018-01-15 adding the RC2 binaries
2018-01-15 Commiting the code with a working SPI port.
2018-01-15 adding the current state of play of the drivers.. pretty shocking but hacked to a reasonable structure.
2018-01-28 Fixed the driver so that it reads in hdtoolbox.
2018-05-16 Correct typo: TerribleFore -> TerribleFire (#12)

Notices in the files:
eagle/SL530.brd:
(C) 2017 S.J Leary
Published under the
GNU Public License (GPL) v2
parts and their libraries:
microbuilder: This work is placed in the public domain, and may be freely used for commercial and non-commercial work with the following conditions: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
SparkFun-Retired: Licensing:Creative Commons ShareAlike 4.0 International - https://creativecommons.org/licenses/by-sa/4.0
